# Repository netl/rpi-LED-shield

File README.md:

#todo
heatsinks for fet and regulator
shunt resistors

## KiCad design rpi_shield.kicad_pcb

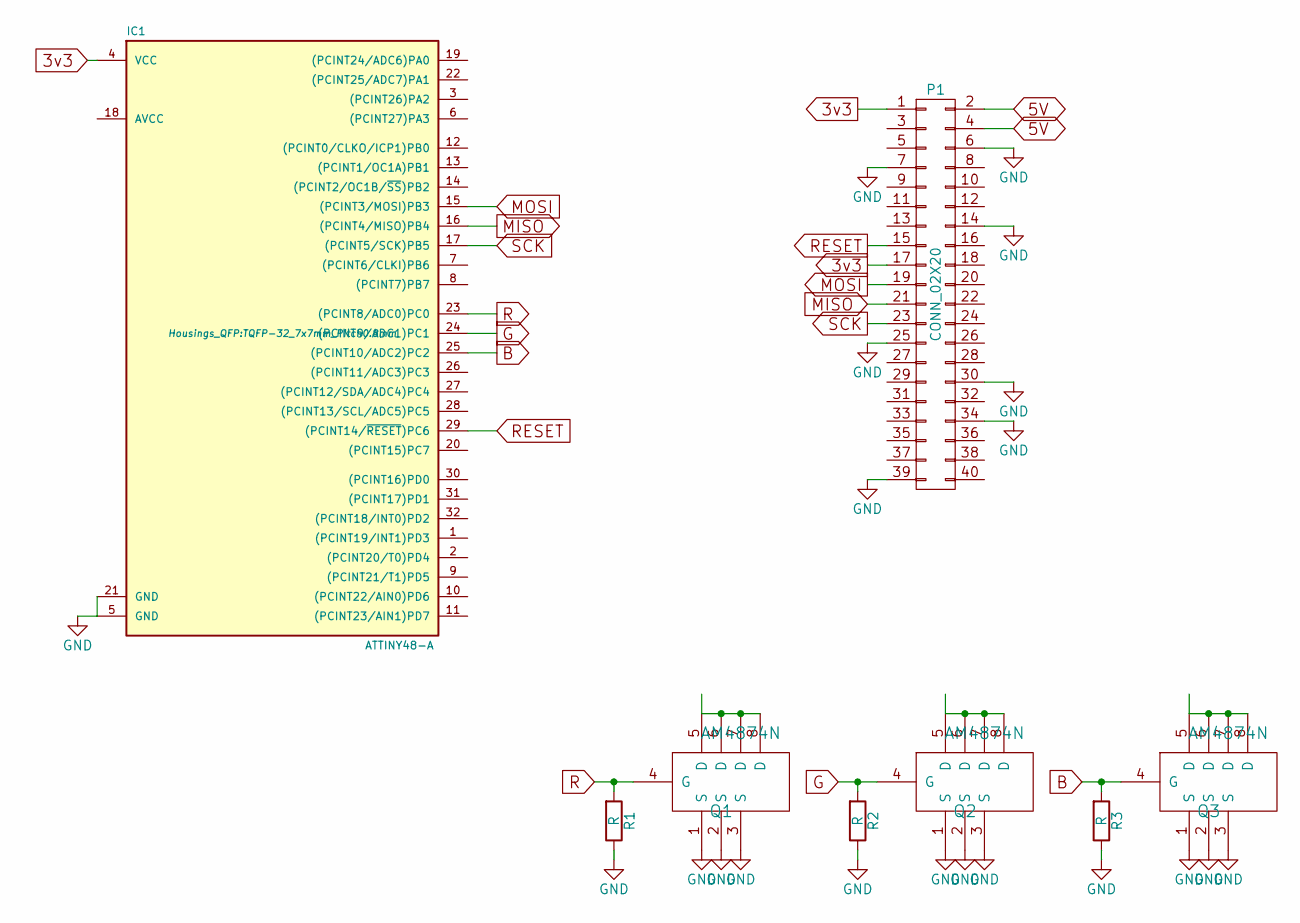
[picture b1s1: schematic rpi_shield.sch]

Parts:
IC1: ATTINY48-A; TQFP-32_7x7mm_Pitch0.8mm
P1: CONN_02X20; Pin_Header_Straight_2x20
Q1, Q2, Q3: AM4874N; SOIC-8_3.9x4.9mm_Pitch1.27mm
R1, R2, R3: R; SMD_0603

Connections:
3v3: IC1.4 (VCC), P1.1, P1.17
5V: P1.2, P1.4
B: IC1.25 ((PCINT10/ADC2)PC2), Q3.4 (G), R3.2
G: IC1.24 ((PCINT9/ADC1)PC1), Q2.4 (G), R2.2
GND: IC1.5 (GND), IC1.21 (GND), P1.6, P1.7, P1.14, P1.25, P1.30, P1.34, P1.39, Q1.1 (S), Q1.2 (S), Q1.3 (S), Q2.1 (S), Q2.2 (S), Q2.3 (S), Q3.1 (S), Q3.2 (S), Q3.3 (S), R1.1, R2.1, R3.1
MISO: IC1.16 ((PCINT4/MISO)PB4), P1.21
MOSI: IC1.15 ((PCINT3/MOSI)PB3), P1.19
unnamed: Q1.5 (D), Q1.6 (D), Q1.7 (D), Q1.8 (D)
unnamed: Q2.5 (D), Q2.6 (D), Q2.7 (D), Q2.8 (D)
unnamed: Q3.5 (D), Q3.6 (D), Q3.7 (D), Q3.8 (D)
R: IC1.23 ((PCINT8/ADC0)PC0), Q1.4 (G), R1.2
RESET: IC1.29 ((PCINT14/~RESET~)PC6), P1.15
SCK: IC1.17 ((PCINT5/SCK)PB5), P1.23

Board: 2 copper layers, 8 parts (0 on the bottom side), 13 nets, no tracks yet.

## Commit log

2015-12-13 cleaned up
2015-12-13 swapped the mcu to a dac and a quad opamp
2015-12-14 removed excess power pins. moved parts around.
2015-12-14 updated pdf and todo
2015-12-14 added cap for opamp
2016-02-08 changed fets, added usb serial
2016-02-08 added schematic for usb serial
2016-02-08 ready for etching!
2016-02-09 cleanup
2016-02-15 started work on 2 layered version
2016-02-15 moved usb header, rerouted a few traces
2016-02-15 first working version
2016-02-15 added gain to current feedback
2016-02-16 removed gain from feedback, added adjust to DAC reference voltage
2016-02-16 added pulldown transistors, moved reference adjust to DAC output
2016-02-16 cleaned up a bit
2016-02-16 now seperate inputs are tweakable
2016-02-16 added power total consumption
2016-03-23 added microcontroller :D
2016-03-24 pwm works now, I think. fixed makefile and tweaked default configuration for led current
2016-03-24 spi works :D
2016-03-25 added smoothing to mcu code, which might be a bad idea. added scripts for analyzing network load
2016-03-27 rgb data is now sent in one byte
2016-03-27 reworked spi protocol
2016-03-27 tons of little tweaks
2016-03-27 cleaned up. thanks sfotrabbit.
2016-03-29 cleaned up a bit, started working on builtin animations
2016-03-30 first working animation
2016-04-12 starting to work on adding the mcu
2016-04-12 removed resistor dividors, added cap to usb
2016-04-18 added mcu
2016-05-11 tweaks on animations
2016-05-11 swapped mcu to atmega48, added debug tools
2016-05-11 changed pwm channels from RGBW mentality to ABCD and made them easier to change
2016-05-11 added GUI example for triggering animations
2016-05-17 updated pdf
2016-07-17 added the voltage dividers back to the constant-current control
2016-07-24 added the damn resistors... again.
2016-07-27 changed current calculations
2016-08-08 working version from assembly 2016
2016-08-26 post assembly commit, everything works. and the moodlight script is kind of nice
2017-04-30 added script for artnet slave
